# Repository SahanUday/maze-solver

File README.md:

# maze-solver
Arduino Mega robot that autonomously explores and shortest-path solves a two-section maze connected by a line-followed bridge.

## Development setup

```
pip install -r requirements-dev.txt
pre-commit install
```

Firmware builds/uploads are handled by the PlatformIO VS Code extension - no separate PlatformIO install needed for that.

## Choosing which parts the robot runs

The run is cut into parts (`AExplore`, `AProve`, `AExit`, `Line`, `BEntry`, `BExplore`, `BProve`;
[ADR 0016](docs/architecture/decisions/0016-cut-the-run-into-parts.md)). The firmware runs the stretch
set by `RUN_PART_FIRST` and `RUN_PART_LAST` in [include/spec/tuning/Run.h](include/spec/tuning/Run.h). The
competition setting is the whole course (`AExplore` to `BProve`). To test one part on the robot, edit the
two constants, flash, and place the robot where the first part expects it:

| FIRST | LAST | What runs | Put the robot |
|---|---|---|---|
| `AExplore` | `BProve` | The whole course (the competition setting). Today it runs `AExplore`, `AExit`, `Line` and stays in `Line`: the line has no end rule yet (#60), so the Section B parts are never reached. | On the Section A start tile |
| `AExplore` | `Line` | Section A, out to the line, then the line | On the Section A start tile |
| `AExplore` | `AExit` | Section A, out to the line, then stop | On the Section A start tile |
| `AExplore` | `AExplore` | Explore until the marker, then stop | On the Section A start tile |
| `Line` | `Line` | Follow the line (no end rule yet, #60) | On the line, past the gap |
| `Line` | `BProve` | The same today. Later it will be the line plus Section B | On the line, past the gap |
| `BEntry` | `BProve` | Section B alone: explore from the entry tile, then prove the path. Host-tested only; with no finish detector yet (#69) it ends when every reachable tile is entered | On the Section B entry tile, facing in, the bridge's opening behind |

Refused selections:

- `AProve`, because it isn't built yet.
- `AExit` or `BProve` as the first part, because they carry on a map and can't start alone.
- A last part before the first, which fails to compile.
- Without a line calibration, the run ends after `AExplore` whatever the last part is, and `Line` alone is refused.

## Bench firmware: check and measure the robot

`tools/bench/bench.cpp` is a separate firmware for the bench: it checks every sensor and motor and
takes the measurements the constants in `include/spec/` need. It runs the mission's own drivers,
perception, motion controller and IR calibration, so what it reads is what the mission sees.

```
pio run -e bench -t upload        # then the serial monitor at 250000 baud, and type h
pio run -e mega -t upload         # put the mission back afterwards
```

Keep the robot still for the first two seconds (the gyro is zeroed). **The motors never move on their
own:** only `o`, `s` and `t` start them, and any key stops them. Hard limits hold whatever the
controller does: duty 600 of 799, 3 s open loop, 20 s and 2100 mm per move, a stop at 130 mm from a
wall ahead, and a stop when a wheel pushes but does not turn.

| Command | What it does |
|---|---|
| `w` | every sensor once, and the slowest tick since the last `w` |
| `v [ms]` | stream that line every `ms` (default 100, down to 10) until any key |
| `z` | zero the odometer and encoder counts (push the robot along a tape, then `w`) |
| `b` | zero the gyro again (hold still) |
| `m [ms] [label]` | hold still and measure: mean, sd, min, max of each IR channel, ultrasonic, the incline and the gyro, plus the heading drift |
| `k`, `f`, `save`, `cal` | IR calibration: start a capture, slide every channel over white and black, finish (in use at once), write it to EEPROM for the mission, show it |
| `o <L> <R> <ms>` | open loop: a fixed signed duty on each wheel; prints the counts and speed per wheel |
| `s <mm> [mm/s]` | closed-loop straight with the mission's controller; prints the time and the error |
| `t <deg>` | closed-loop turn in place, CCW positive |
| `p`, `h`, `x` | settings, help, stop |

Lines starting with `#` are for people; the rest are CSV whose first field says what they are
(`status`, `stat`, `open`, `move`, `result`, `cal`), so a saved log can be split with `grep`. Lift
the wheels off the floor for the first `o` and `s`.

## Testing and checks

Commits are checked automatically by pre-commit, and every pull request runs the
full set in CI. What each check is, how to run it yourself, and what to do when
one fails: [docs/testing.md](docs/testing.md).

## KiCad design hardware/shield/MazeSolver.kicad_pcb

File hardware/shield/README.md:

# Mega shield PCB

A two-layer, through-hole board that plugs onto the Arduino Mega 2560 and gives every module a
labelled header, plus the operator panel (START, MODE DIP, two LEDs), a RESET button and the Mega's
5 V switch. Why it is built this way: [ADR 0023](../../docs/architecture/decisions/0023-shield-pcb-for-the-mega.md)
(the shield) and [ADR 0024](../../docs/architecture/decisions/0024-the-mega-5v-on-its-own-switch.md)
(the Mega's 5 V switch and the motor pull-downs).

**Status:** designed 2026-11-26. Not yet made or tested.

## Files

| File | What it is |
|---|---|
| `MazeSolver.kicad_pro` / `.kicad_sch` / `.kicad_pcb` | The KiCad 10 project, schematic and board |
| `fp-lib-table`, `Arduino_MountingHole.pretty/` | The project footprint library (the Mega's mounting holes) |
| `fab/` | Gerber and drill files for the factory, generated from this board revision |

Open `MazeSolver.kicad_pro` in KiCad 10. Every other footprint is from KiCad's standard library.

## The board

- 91.1 × 53.3 mm, 2 layers, all through-hole. The headers to the Mega (J1–J7) sit on the underside;
  everything else is on top.
- Tracks are 0.3 mm for signals and 0.8 mm for `+5V` and `MEGA_5V`, with GND poured on both layers.
- The left end is trimmed, so nothing sits over the Mega's USB socket or power jack.

## Connectors

The pin order is printed on the board next to each header. Pin numbers are the firmware's
([`PinMap.h`](../../include/spec/pins/PinMap.h)).

| Header | Board label | Pins, pin 1 first | Mega pins |
|---|---|---|---|
| J8 | 5V IN | +5V, GND | From the LM2596 buck output |
| J9 / J10 / J11 | US FRONT / LEFT / RIGHT | 5V, TRG, ECH, GND | Trig 30 / 32 / 34, echo A10 / A11 / A12 |
| J12 | LINE SENSOR | GND, IR, D1–D8, 5V | Emitter 36, D1–D8 on A0–A7 (D1 = the robot's left) |
| J13 | IMU | 5V, GND, SCL, SDA, XDA, XCL, AD0, INT | SCL 21, SDA 20; the last four are not connected |
| J14 | MOTOR L | RPWM, LPWM, EN, EN, 5V, GND | 6, 7, EN 8 |
| J15 | MOTOR R | RPWM, LPWM, EN, EN, 5V, GND | 11, 12, EN 10 |
| J16 / J17 | ENC L / ENC R | 5V, A, B, GND | 2, 3 / 19, 18 |

Wire each cable to the module's own labels. In particular, the IBT-2 header is RPWM, LPWM, R_EN, L_EN,
R_IS, L_IS, VCC, GND: shield pins 5V and GND go to the IBT-2's **VCC and GND (its pins 7 and 8)**, not
its pins 5 and 6.

## Switches, buttons and LEDs

| Part | Board label | What it does |
|---|---|---|
| SW1 | START | Starts a run (D38). Ignored while `BUTTON_WIRED` is `false` in `spec/pins/Wired.h` |
| SW2 | MODE: 1 RUN 2 FAST 3 CAL 4 RES | The mode, read while the robot waits (D40–D43). Meanings: [panel](../../docs/architecture/modules/panel.md) |
| SW3 | RESET | Resets the Mega (RESET to GND). The shield covers the Mega's own button |
| SW4 | MEGA 5V | Connects the Mega's 5 V pins to the battery 5 V. See [Power](#power) |
| D1 + R1 | STATUS | Green LED on D26 |
| D2 + R2 | ERROR | Red LED on D27 |
| R3 / R4 | — | 10 kΩ pull-downs on D8 / D10: the motors stay off while the Mega is not driving them |

## Power

```
Buck 5V ── J8 ── +5V ── sensors, encoders, motor-driver logic   (always on the battery)
                  └──[SW4]── MEGA_5V ── Mega 5V pins (J1 pin 5, J7 pins 35/36)
```

| SW4 | USB | Use |
|---|---|---|
| ON | unplugged | **Running.** Everything on the battery |
| OFF | plugged in | **Upload and serial.** The Mega on USB, the sensors on the battery |
| ON | plugged in | **Never.** It joins the battery 5 V to the laptop's USB |

- **Before plugging in USB:** turn SW4 OFF. **Before running:** unplug USB, then turn SW4 ON.
- With SW4 OFF the sensors still need the battery: battery on first, then reset (the IMU).
- Calibrate the line sensor with SW4 ON on the battery. On USB the array and the Mega use different
  5 V supplies, so the readings are not ratiometric.
- Don't leave the battery on with SW4 OFF and no USB: the sensors are powered and the Mega is not.

## Parts

| Ref | Part | Qty |
|---|---|---|
| J1, J3, J4, J5, J6 | Male header 1×8, 2.54 mm (to the Mega) | 5 |
| J2 | Male header 1×10, 2.54 mm (to the Mega) | 1 |
| J7 | Male header 2×18, 2.54 mm (to the Mega) | 1 |
| J9, J10, J11, J16, J17 | Male header 1×4, 2.54 mm | 5 |
| J14, J15 | Male header 1×6, 2.54 mm | 2 |
| J13 | Male header 1×8, 2.54 mm | 1 |
| J12 | Male header 1×11, 2.54 mm | 1 |
| J8 | Screw terminal, 2-way, 5.08 mm (Phoenix MKDS 1,5 or similar) | 1 |
| SW1, SW3 | Tactile push button, 6 × 6 mm | 2 |
| SW2 | DIP switch, 4-way, 2.54 mm | 1 |
| SW4 | DIP switch, 1-way, 2.54 mm, rated 100 mA or more | 1 |
| D1 | LED 5 mm, green | 1 |
| D2 | LED 5 mm, red | 1 |
| R1, R2 | Resistor 470 Ω, 0.25 W | 2 |
| R3, R4 | Resistor 10 kΩ, 0.25 W | 2 |

## Ordering

Upload a zip of `fab/` and choose 2 layers, 1.6 mm, HASL, 1 oz copper. Any mask colour works.

Before ordering:

1. Print the board at 100 % and lay it on a Mega: the headers, holes and the USB end must line up.
2. Check SW4's datasheet: 100 mA or more.
3. Get the instructor's approval for the added controls (rules, p. 7).

## Changing the board

Edit in KiCad, then in the PCB editor refill the zones (**B**) and run the DRC with the schematic
parity check. The expected report is:

- 2 unconnected items: the J6 copy of SDA/SCL, left unrouted on purpose (the Mega joins it to J2
  inside). Exclude them.
- 4 silkscreen warnings on the Mega headers' reference text (J2, J4, J7).

Then regenerate `fab/` in the same commit, so it always matches the board:

```
cd hardware/shield
kicad-cli pcb export gerbers -o fab/ --layers F.Cu,B.Cu,F.Mask,B.Mask,F.SilkS,B.SilkS,Edge.Cuts MazeSolver.kicad_pcb
kicad-cli pcb export drill -o fab/ --format excellon --excellon-separate-th --excellon-units mm --excellon-oval-format route MazeSolver.kicad_pcb
```

A pin moved in `PinMap.h` needs the same change here, and a new board revision.

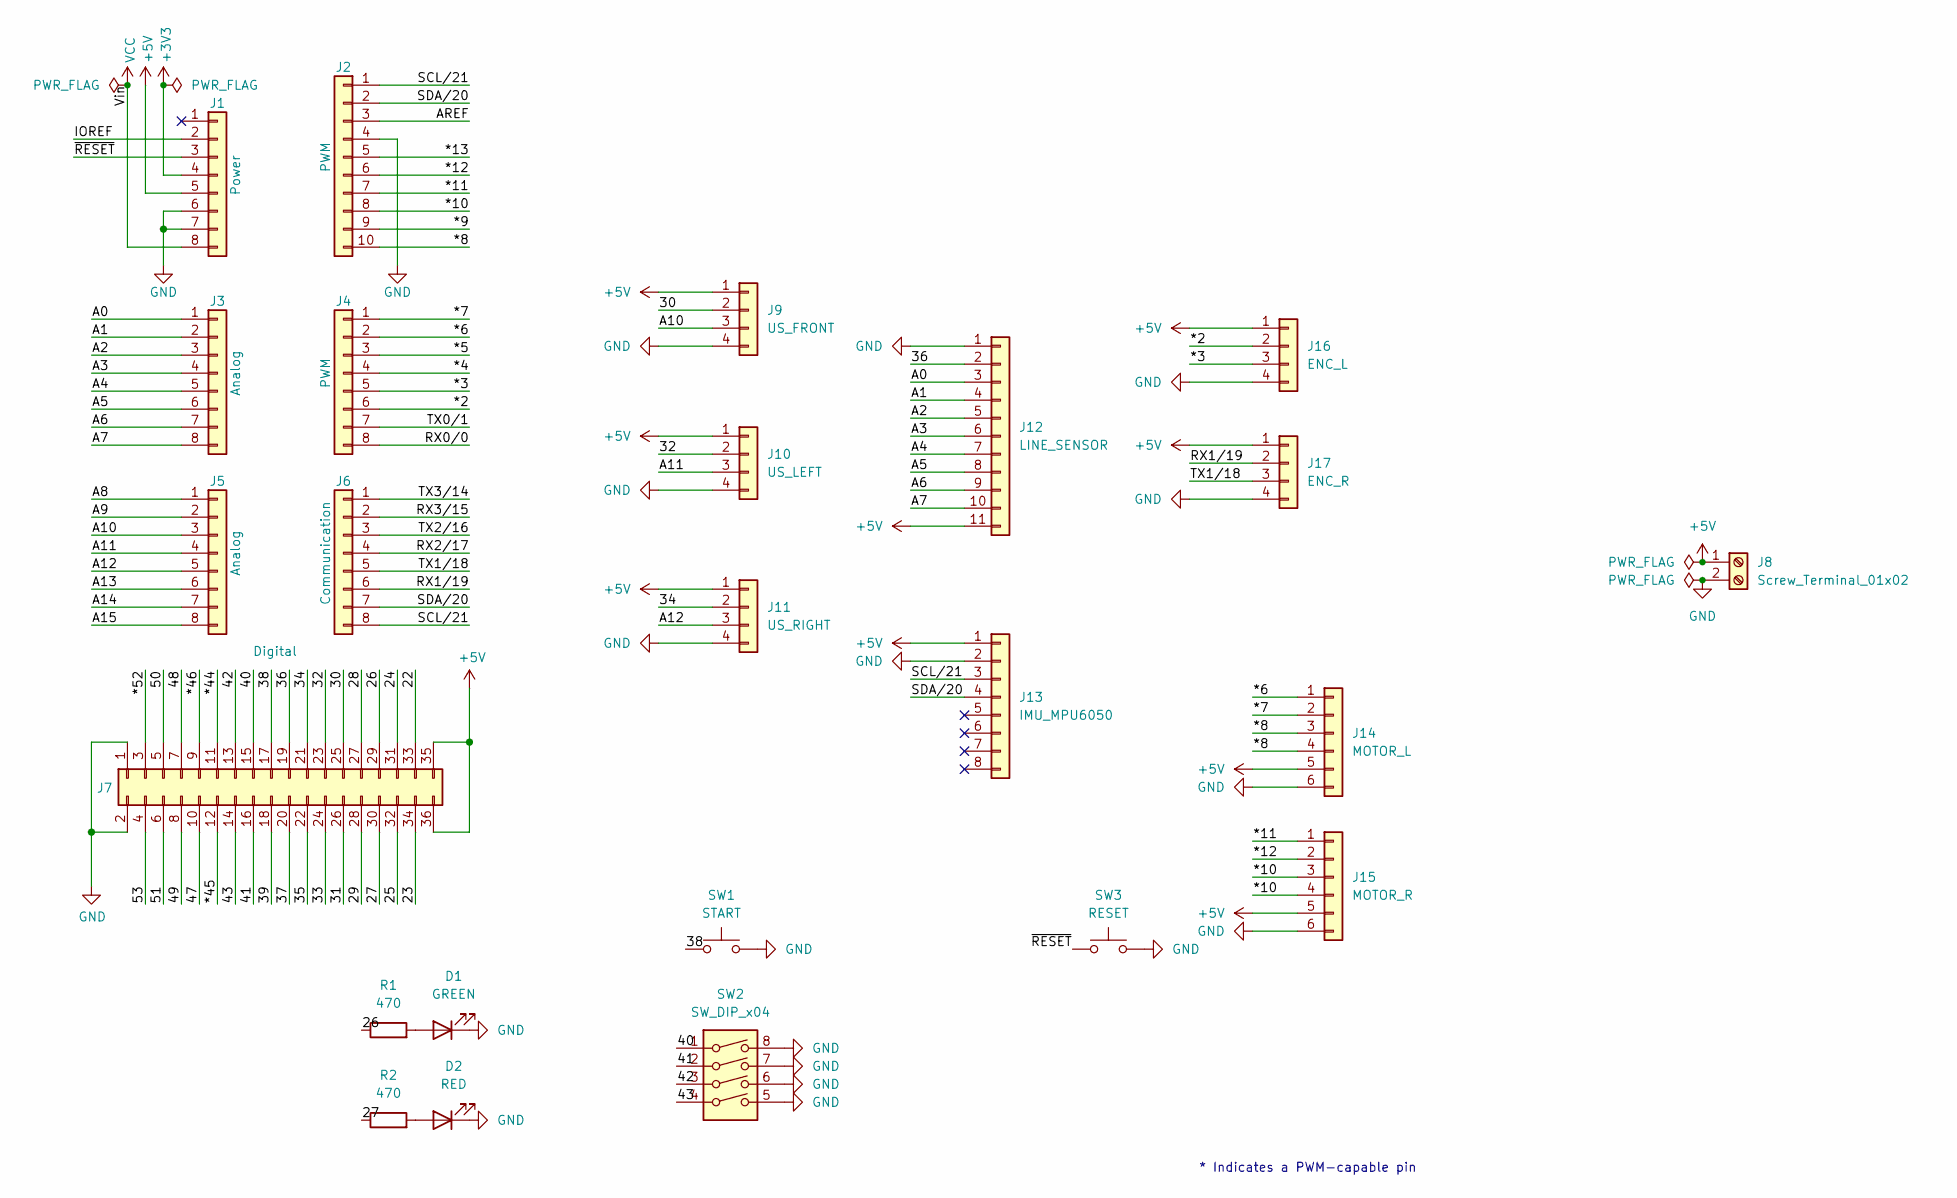
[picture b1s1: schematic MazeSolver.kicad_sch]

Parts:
D1: GREEN; LED_D5.0mm
D2: RED; LED_D5.0mm
J1: Power; PinHeader_1x08_P2.54mm_Vertical
J2: PWM; PinHeader_1x10_P2.54mm_Vertical
J3, J5: Analog; PinHeader_1x08_P2.54mm_Vertical
J4: PWM; PinHeader_1x08_P2.54mm_Vertical
J6: Communication; PinHeader_1x08_P2.54mm_Vertical
J7: Digital; PinHeader_2x18_P2.54mm_Vertical
J8: Screw_Terminal_01x02; TerminalBlock_Phoenix_MKDS-1,5-2-5.08_1x02_P5.08mm_Horizont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
J9: US_FRONT; PinHeader_1x04_P2.54mm_Vertical
J10: US_LEFT; PinHeader_1x04_P2.54mm_Vertical
J11: US_RIGHT; PinHeader_1x04_P2.54mm_Vertical
J12: LINE_SENSOR; PinHeader_1x11_P2.54mm_Vertical
J13: IMU_MPU6050; PinHeader_1x08_P2.54mm_Vertical
J14: MOTOR_L; PinHeader_1x06_P2.54mm_Vertical
J15: MOTOR_R; PinHeader_1x06_P2.54mm_Vertical
J16: ENC_L; PinHeader_1x04_P2.54mm_Vertical
J17: ENC_R; PinHeader_1x04_P2.54mm_Vertical
R1, R2: 470; R_Axial_DIN0207_L6.3mm_D2.5mm_P10.16mm_Horizontal
SW1: START; SW_PUSH_6mm
SW2: SW_DIP_x04; SW_DIP_SPSTx04_Slide_9.78x12.34mm_W7.62mm_P2.54mm
SW3: RESET; SW_PUSH_6mm

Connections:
+3V3: J1.4
+5V: J1.5, J7.35, J7.36, J8.1, J9.1, J10.1, J11.1, J12.11, J13.1, J14.5, J15.5, J16.1, J17.1
/22: J7.33
/23: J7.34
/24: J7.31
/25: J7.32
/26: J7.29, R1.1
/27: J7.30, R2.1
/28: J7.27
/29: J7.28
/30: J7.25, J9.2
/31: J7.26
/32: J7.23, J10.2
/33: J7.24
/34: J7.21, J11.2
/35: J7.22
/36: J7.19, J12.2
/37: J7.20
/38: J7.17, SW1.1
/39: J7.18
/40: J7.15, SW2.1
/41: J7.16, SW2.2
/42: J7.13, SW2.3
/43: J7.14, SW2.4
/47: J7.10
/48: J7.7
/49: J7.8
/50: J7.5
/51: J7.6
/53: J7.4
/*2: J4.6, J16.2
/*3: J4.5, J16.3
/*4: J4.4
/*5: J4.3
/*6: J4.2, J14.1
/*7: J4.1, J14.2
/*8: J2.10, J14.3, J14.4
/*9: J2.9
/*10: J2.8, J15.3, J15.4
/*11: J2.7, J15.1
/*12: J2.6, J15.2
/*13: J2.5
/*44: J7.11
/*45: J7.12
/*46: J7.9
/*52: J7.3
/A0: J3.1, J12.3
/A1: J3.2, J12.4
/A2: J3.3, J12.5
/A3: J3.4, J12.6
/A4: J3.5, J12.7
/A5: J3.6, J12.8
/A6: J3.7, J12.9
/A7: J3.8, J12.10
/A8: J5.1
/A9: J5.2
/A10: J5.3, J9.3
/A11: J5.4, J10.3
/A12: J5.5, J11.3
/A13: J5.6
/A14: J5.7
/A15: J5.8
/AREF: J2.3
/IOREF: J1.2
/RX0/0: J4.8
/RX1/19: J6.6, J17.2
/RX2/17: J6.4
/RX3/15: J6.2
/SCL/21: J2.1, J6.8, J13.3
/SDA/20: J2.2, J6.7, J13.4
/TX0/1: J4.7
/TX1/18: J6.5, J17.3
/TX2/16: J6.3
/TX3/14: J6.1
/~RESET: J1.3, SW3.1
GND: D1.1 (K), D2.1 (K), J1.6, J1.7, J2.4, J7.1, J7.2, J8.2, J9.4, J10.4, J11.4, J12.1, J13.2, J14.6, J15.6, J16.4, J17.4, SW1.2, SW2.5, SW2.6, SW2.7, SW2.8, SW3.2
unnamed: D1.2 (A), R1.2
unnamed: D2.2 (A), R2.2
VCC: J1.8

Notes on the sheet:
* Indicates a PWM-capable pin

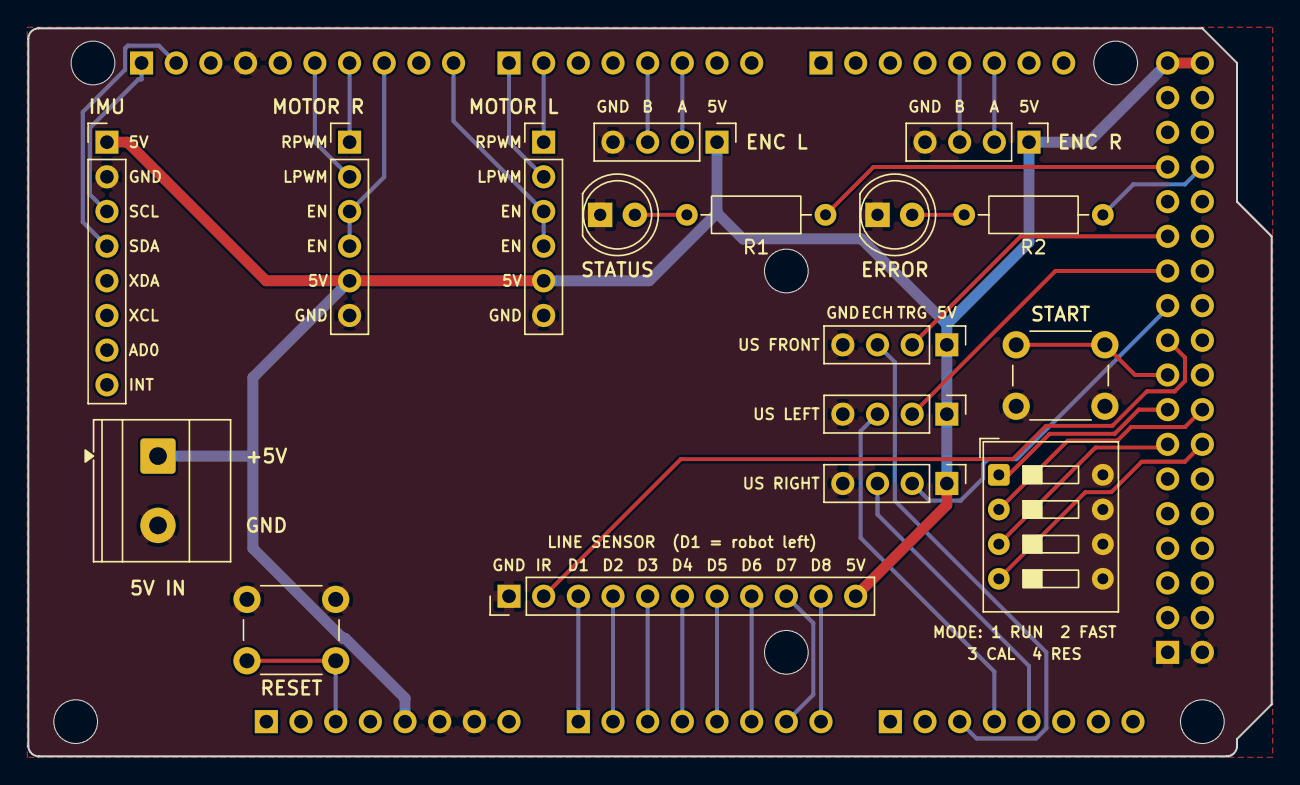
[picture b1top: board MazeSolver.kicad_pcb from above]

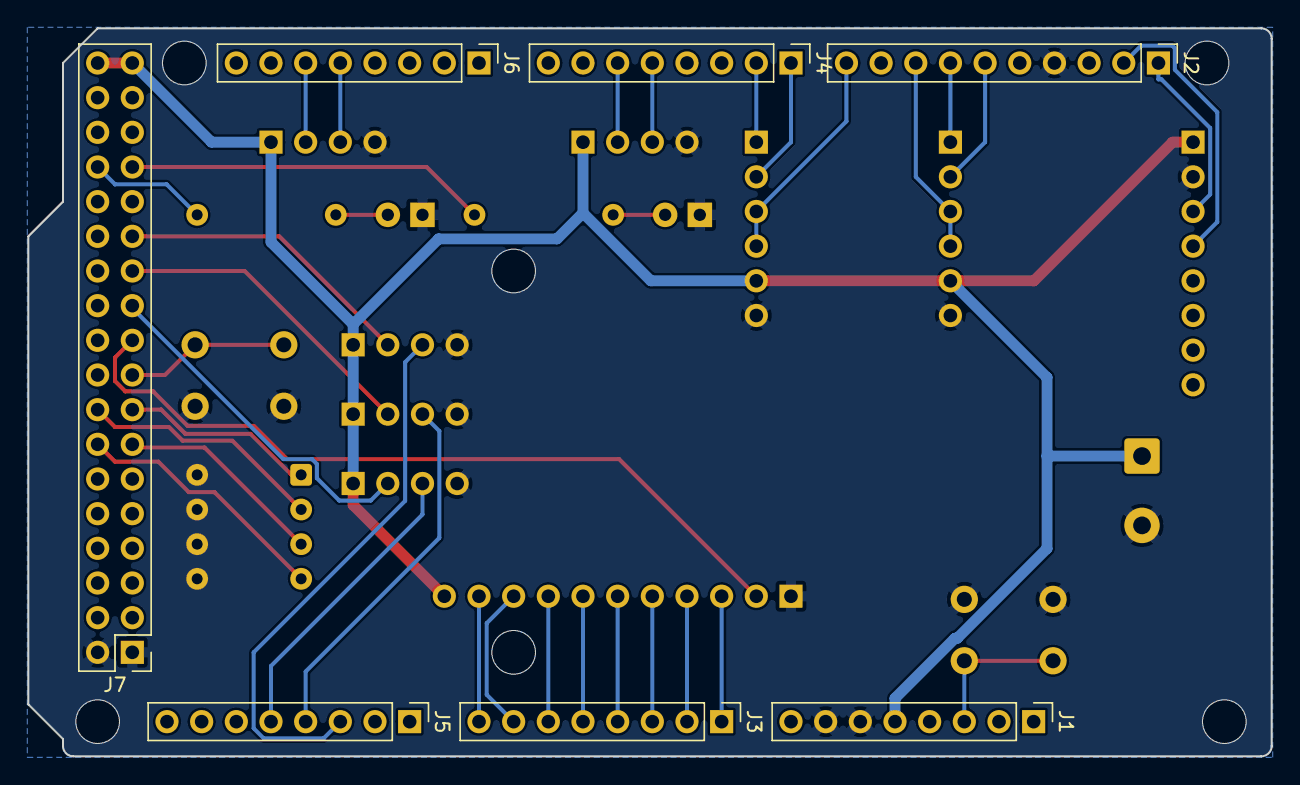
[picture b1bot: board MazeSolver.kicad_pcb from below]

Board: 2 copper layers, 91.1 x 53.3 mm, 30 parts (7 on the bottom side), 39 nets.

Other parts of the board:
MH1, MH2, MH3, MH4, MH5, MH6: MountingHole_3.2mm
